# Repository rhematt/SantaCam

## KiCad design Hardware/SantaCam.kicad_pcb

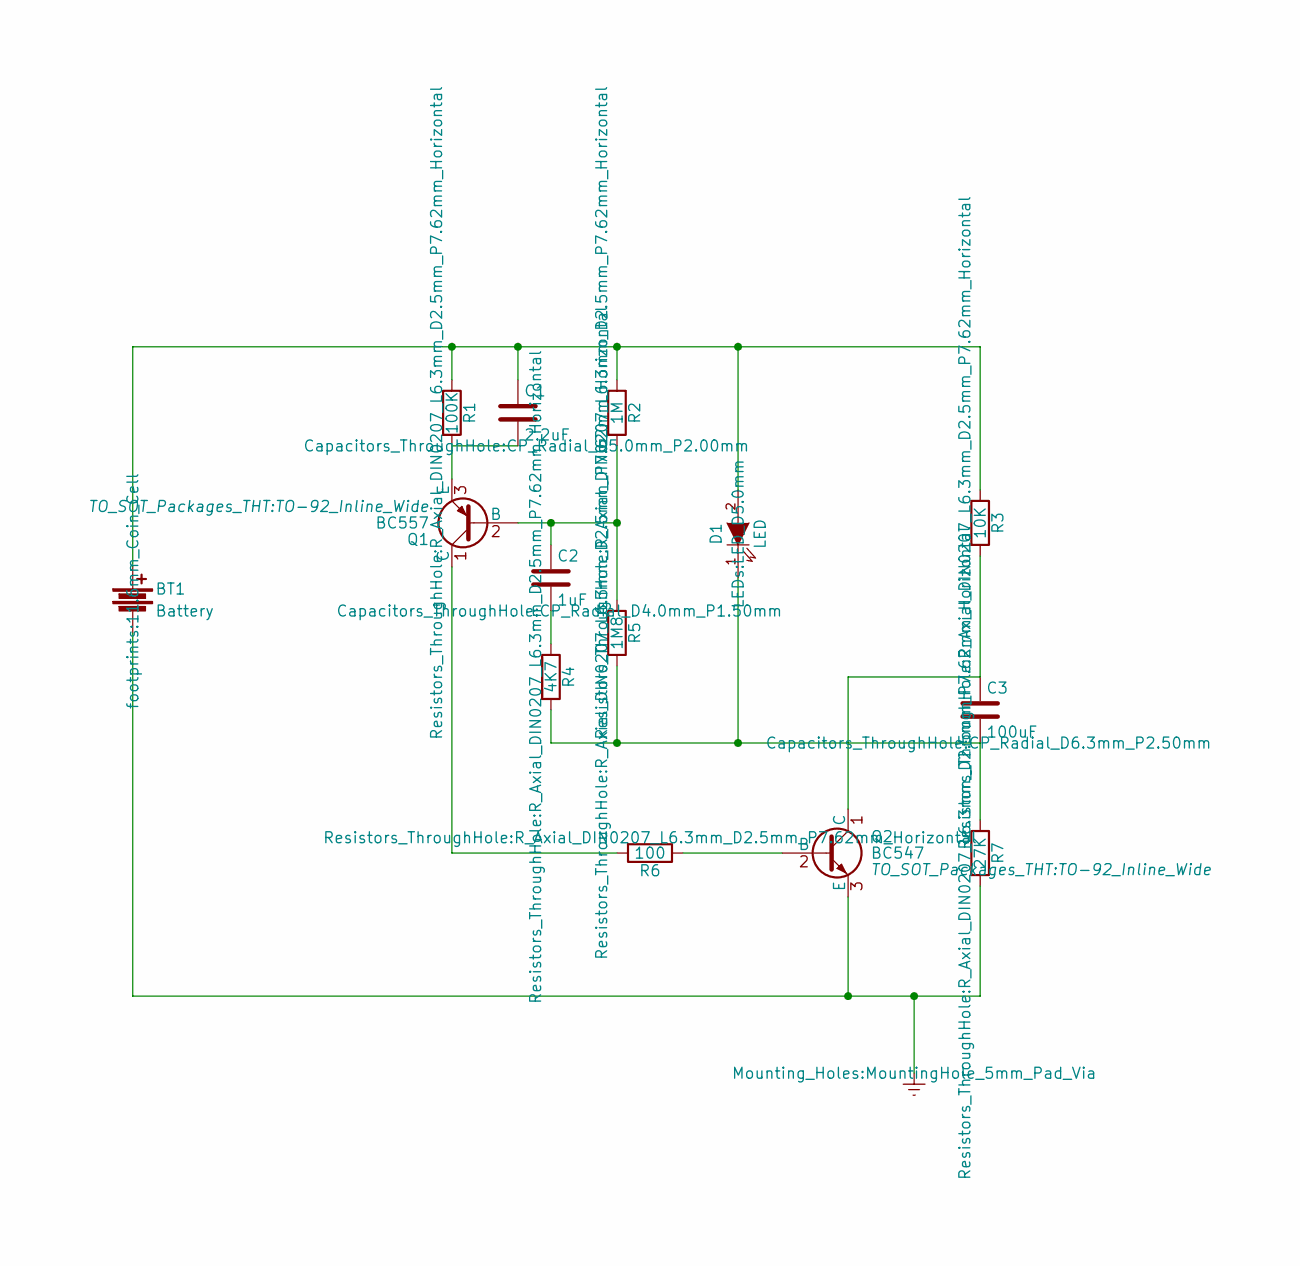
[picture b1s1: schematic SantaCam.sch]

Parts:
BT1: Battery; 11.6mm_Coin_Cell
C1: 2.2uF; CP_Radial_D5.0mm_P2.00mm
C2: 1uF; CP_Radial_D4.0mm_P1.50mm
C3: 100uF; CP_Radial_D6.3mm_P2.50mm
D1: LED; LED_D5.0mm
Q1: BC557; TO-92_Inline_Wide
Q2: BC547; TO-92_Inline_Wide
R1: 100K; R_Axial_DIN0207_L6.3mm_D2.5mm_P7.62mm_Horizontal
R2: 1M; R_Axial_DIN0207_L6.3mm_D2.5mm_P7.62mm_Horizontal
R3: 10K; R_Axial_DIN0207_L6.3mm_D2.5mm_P7.62mm_Horizontal
R4: 4K7; R_Axial_DIN0207_L6.3mm_D2.5mm_P7.62mm_Horizontal
R5: 1M8; R_Axial_DIN0207_L6.3mm_D2.5mm_P7.62mm_Horizontal
R6: 100; R_Axial_DIN0207_L6.3mm_D2.5mm_P7.62mm_Horizontal
R7: 27K; R_Axial_DIN0207_L6.3mm_D2.5mm_P7.62mm_Horizontal

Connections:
Earth: BT1.2, Q2.3 (E), R7.2
unnamed: BT1.1, C1.1, D1.2 (A), R1.1, R2.1, R3.1
unnamed: C1.2, Q1.3 (E), R1.2
unnamed: C2.1, Q1.2 (B), R2.2, R5.1
unnamed: C2.2, R4.1
unnamed: C3.1, Q2.1 (C), R3.2
unnamed: C3.2, D1.1 (K), R4.2, R5.2, R7.1
unnamed: Q1.1 (C), R6.2
unnamed: Q2.2 (B), R6.1

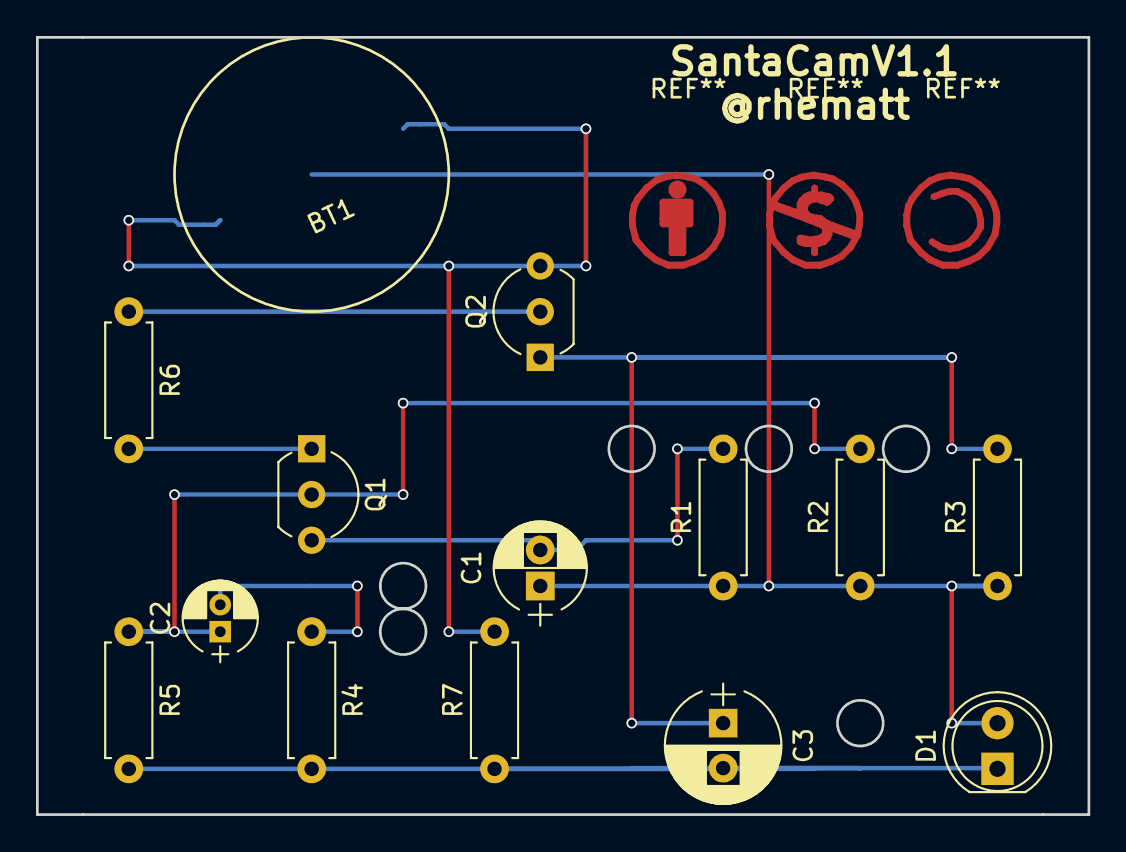
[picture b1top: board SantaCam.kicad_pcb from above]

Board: 2 copper layers, 58.4 x 43.2 mm, 14 parts (0 on the bottom side), 9 nets.

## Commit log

2023-01-15 init
